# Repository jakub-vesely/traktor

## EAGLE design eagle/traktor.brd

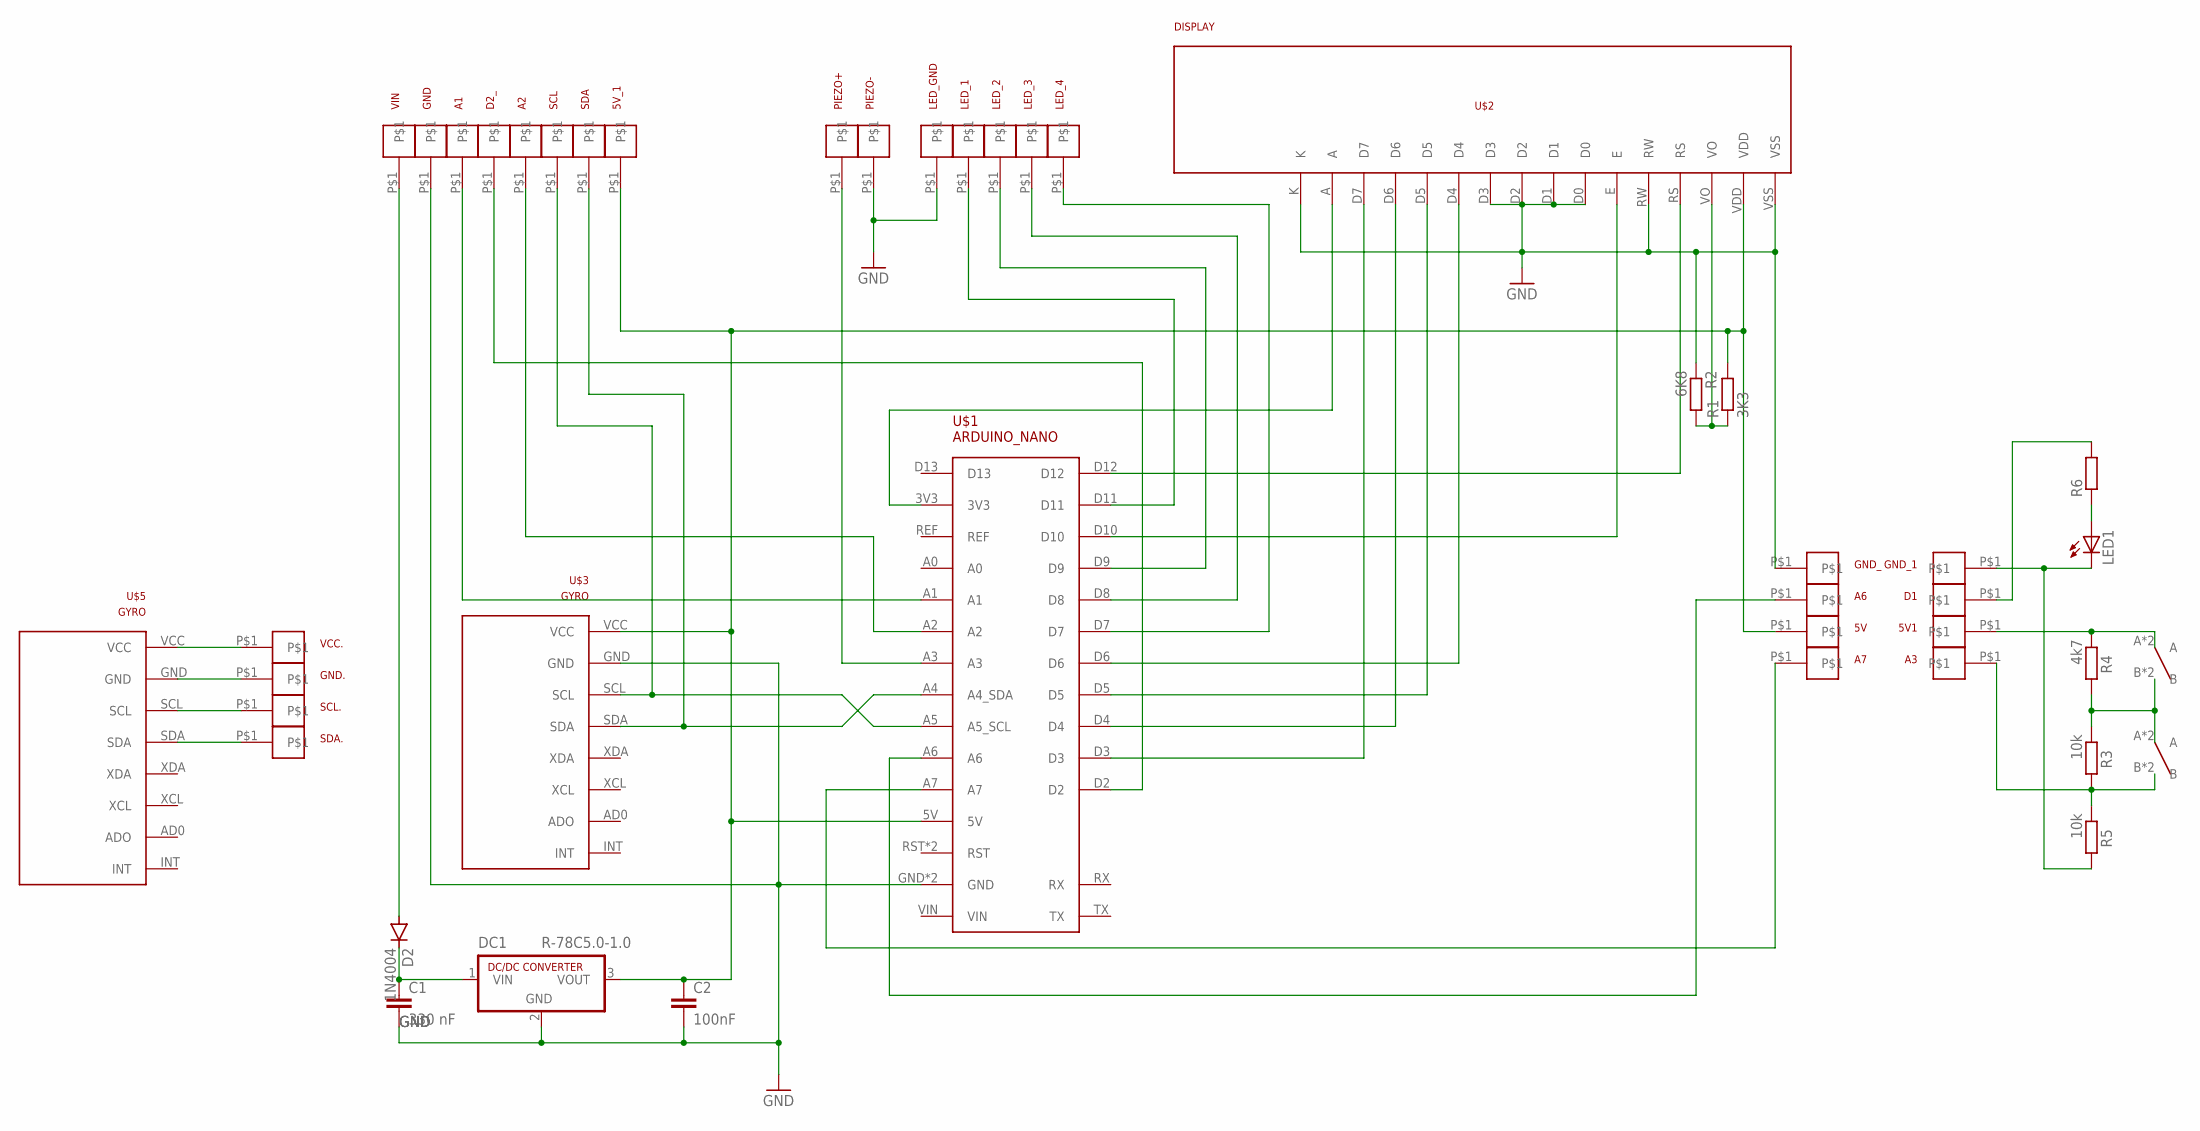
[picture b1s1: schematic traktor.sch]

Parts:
5V, 5V1, 5V_1: I_O_PIN
A1, A2, A3, A6, A7: I_O_PIN
C1: 330 nF; C0805
C2: 100nF; C0805
D1, D2_: I_O_PIN
D2: 1N4004; DO41-10
DC1: R-78C5.0-1.0; SIP3
GND, GND.: I_O_PIN
GND_, GND_1: I_O_PIN
LED1: LED5MM
LED_1, LED_2, LED_3, LED_4: I_O_PIN
LED_GND: I_O_PIN
PIEZO+: I_O_PIN
PIEZO-: I_O_PIN
R1: 3K3; R0603
R2: 6K8; R0603
R3, R5: 10k; R0805
R4: 4k7; R0805
R6: R-EU_R0805; R0805
SCL, SCL.: I_O_PIN
SDA, SDA.: I_O_PIN
U$1: ARDUINO_NANO
U$2: DISPLAY
U$3, U$5: GYRO
U$4, U$6: BUTTON
VCC.: I_O_PIN
VIN: I_O_PIN

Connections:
5V: 5V.P$1, 5V_1.P$1, C2.1, DC1.3 (VOUT), R1.2, U$1.5V, U$2.VDD, U$3.VCC
GND: C1.2, C2.2, DC1.2 (GND), GND.P$1, GND_.P$1, LED_GND.P$1, PIEZO-.P$1, R2.1, U$1.GND, U$1.GND2 (GND), U$2.D0, U$2.D1, U$2.D2, U$2.D3, U$2.K, U$2.RW, U$2.VSS, U$3.GND
GND1: GND_1.P$1, LED1.K (C), R5.2
unnamed: A2.P$1, U$1.A2
unnamed: U$1.3V3, U$2.A
unnamed: U$1.D3, U$2.D7
unnamed: U$1.D4, U$2.D6
unnamed: U$1.D5, U$2.D5
unnamed: U$1.D6, U$2.D4
unnamed: U$1.D10, U$2.E
unnamed: U$1.D12, U$2.RS
unnamed: A7.P$1, U$1.A7
unnamed: R1.1, R2.2, U$2.VO
unnamed: SDA.P$1, U$1.A4 (A4_SDA), U$3.SDA
unnamed: SCL.P$1, U$1.A5 (A5_SCL), U$3.SCL
unnamed: C1.1, D2.C, DC1.1 (VIN)
unnamed: D2_.P$1, U$1.D2
unnamed: A1.P$1, U$1.A1
unnamed: PIEZO+.P$1, U$1.A3
unnamed: A6.P$1, U$1.A6
unnamed: A3.P$1, R3.2, R5.1, U$4.B, U$4.BB (B)
unnamed: R3.1, R4.1, U$4.A, U$4.AA (A), U$6.B, U$6.BB (B)
unnamed: 5V1.P$1, R4.2, U$6.A, U$6.AA (A)
unnamed: LED1.A, R6.1
unnamed: D1.P$1, R6.2
unnamed: LED_1.P$1, U$1.D11
unnamed: LED_2.P$1, U$1.D9
unnamed: LED_3.P$1, U$1.D8
unnamed: LED_4.P$1, U$1.D7
unnamed: U$5.VCC, VCC..P$1
unnamed: GND..P$1, U$5.GND
unnamed: SCL..P$1, U$5.SCL
unnamed: SDA..P$1, U$5.SDA
VIN: D2.A, VIN.P$1

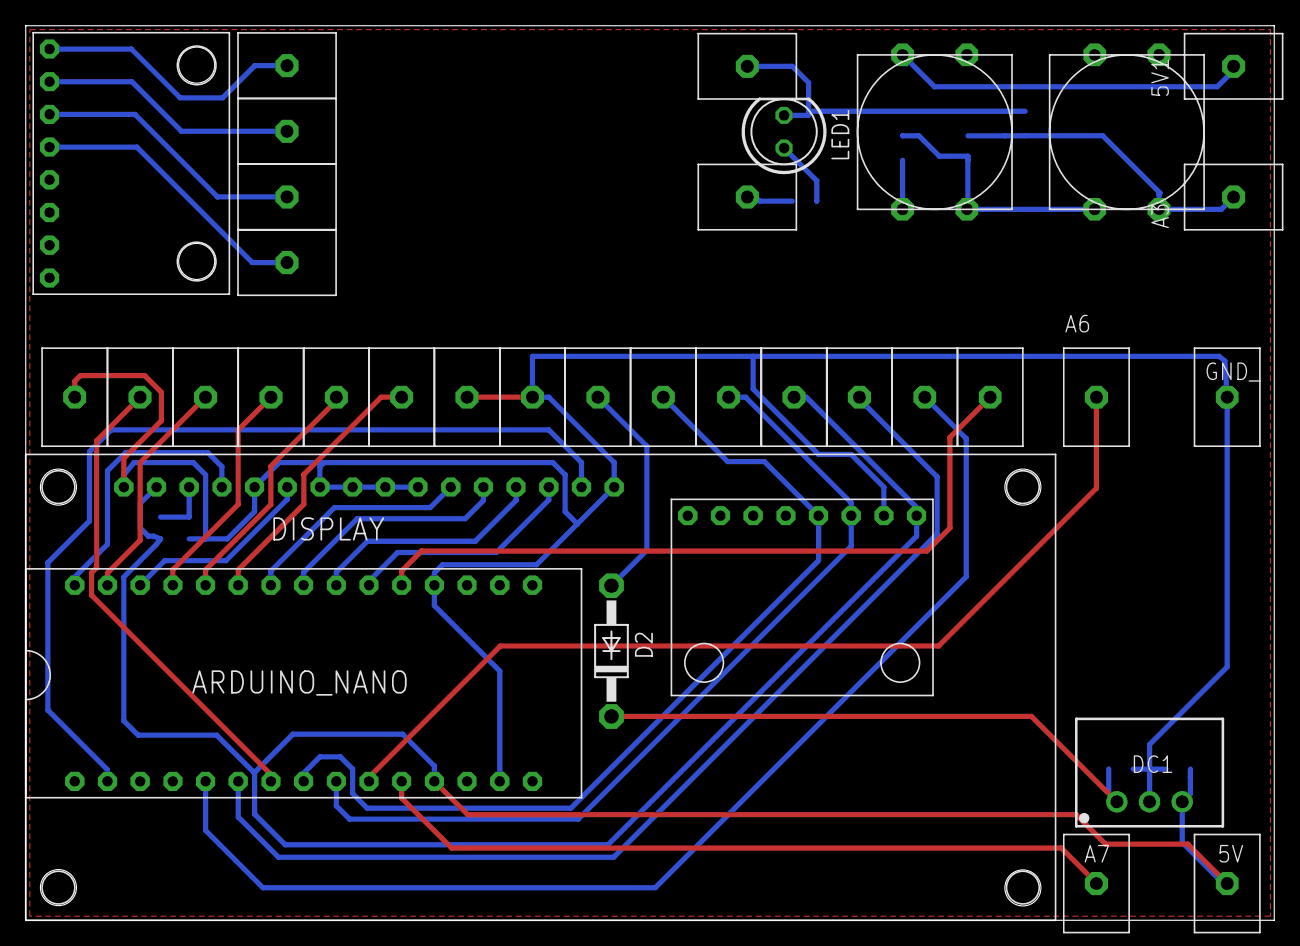
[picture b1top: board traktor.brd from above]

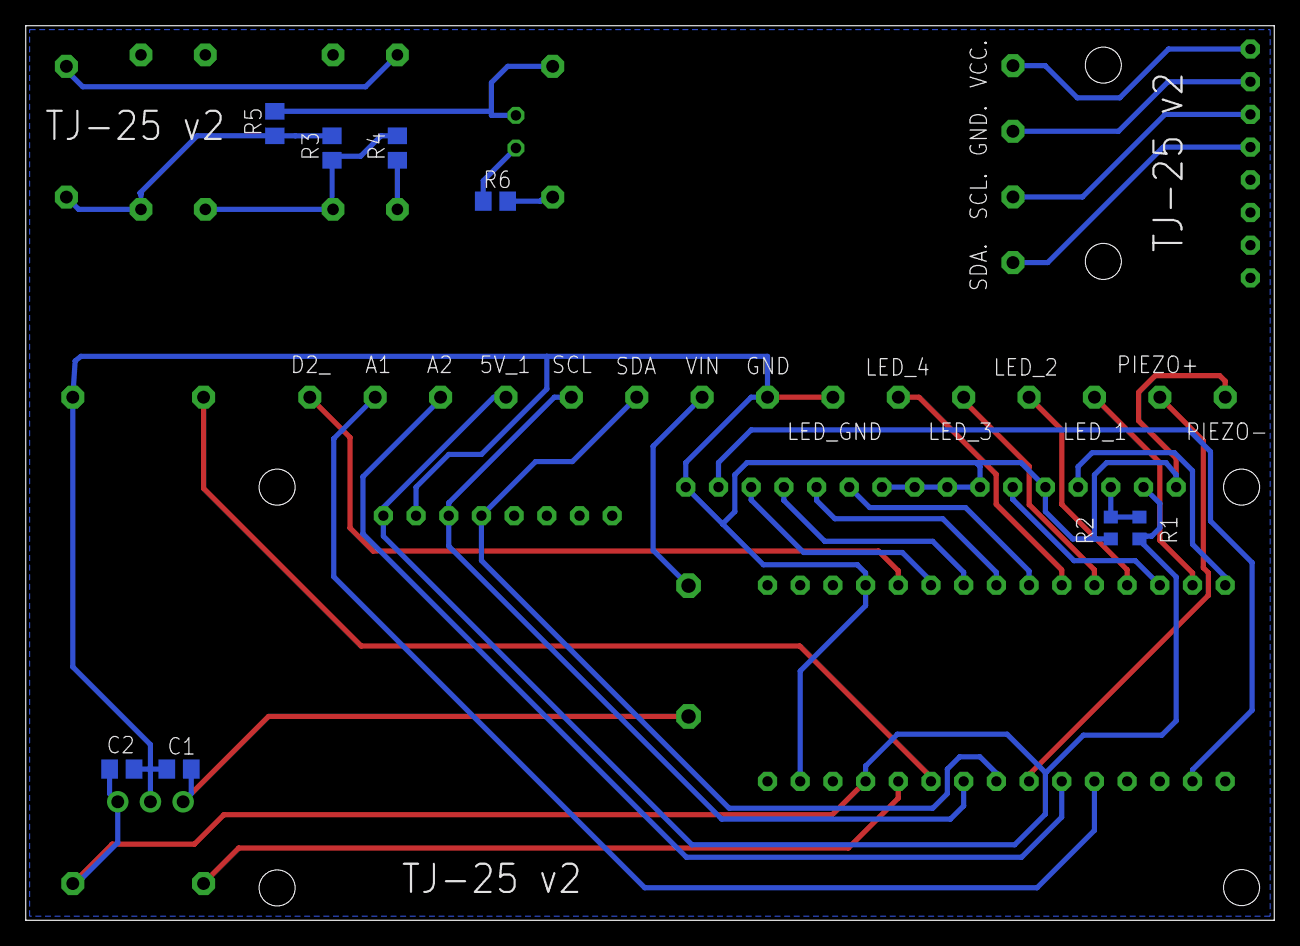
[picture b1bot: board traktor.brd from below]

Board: 2 copper layers, 97.0 x 69.5 mm, 44 parts (8 on the bottom side), 34 nets.

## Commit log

2016-10-09 first version
2017-04-15 adjustments for a new PCB with a new MPU6050
2018-05-05 secound version
2018-05-05 5V Instead Of D13
2018-10-13 added 7805
2018-10-13 updavy pro zirafu
2018-10-14 added pressure limit
2018-12-27 buzzer
2018-12-27 changed to eagle version 9.02
2023-01-02 new board for the traktor project
2023-04-28 updated MPU + basic functionality for Hall sensor
2023-06-10 changes for external MPU and LED bar - PCB redesigned to two layer one
2024-02-06 version 2023-05-04
2024-02-12 fixed storing rotation count
